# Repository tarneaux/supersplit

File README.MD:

# supersplit
You can read the article about this [here](https://tarneo.fr/posts/split_keyboard).

## What is this?
I tried to make a keyboard that is easy to use and compact. For this it has an (oversized) 9-key thumbfan and a (non-oversized) 4x6 matrix.

## Features
- 9-key thumbfan
- 4x6 matrix
- 2 trrs jacks on each side (four in total) for flexibility: on each side you can choose which one to use
- 2 elite-c controllers -> usb-c

## Downsides of this layout
As soon as I had soldered the keyboard, I noticed that the 4 outer thumb keys (On the right on the picture) were hard to reach and I am still not using them after a month of using this keyboard.
The 2 that are just next to the thumb home (the next 2 on the left of the previous) are easier to use but I prefer to use the 2 inner.
In short, that means I could have saved 6 keys on each side's thumfan.

## What I would do differently
I would let the matrix as is, remove the 4 outer thumfan keys and add a few degrees to the angle added to the next 2.

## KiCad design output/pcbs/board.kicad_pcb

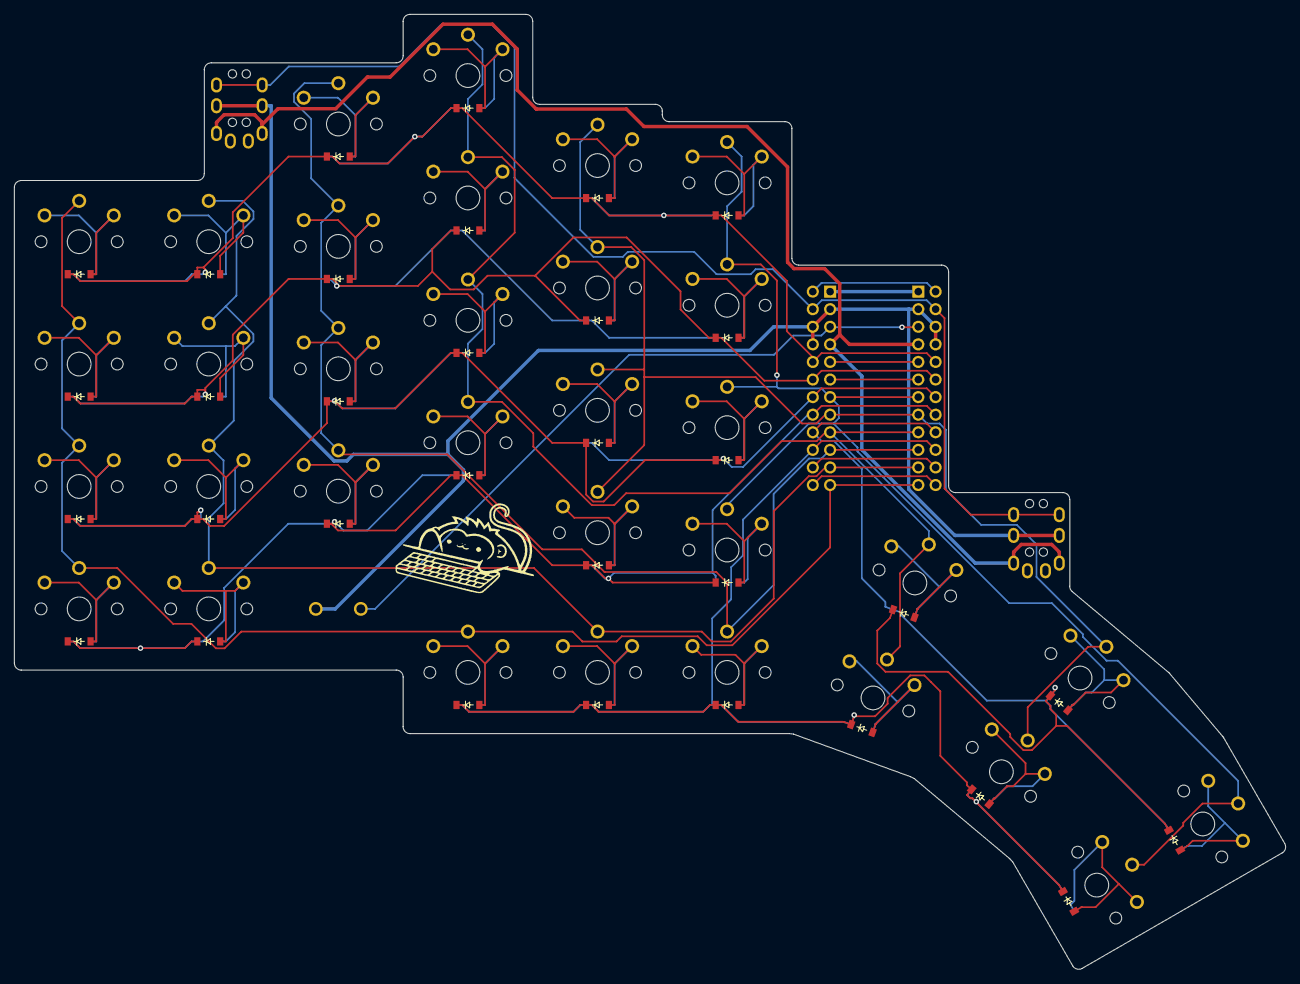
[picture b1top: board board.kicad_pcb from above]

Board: 2 copper layers, 183.6 x 137.9 mm, 73 parts (0 on the bottom side), 55 nets.

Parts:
B1: ResetSW
D1, D2, D3, D4, D5, D6, D7, D8, D9, D10, D11, D12, D13, D14, D15, D16, D17, D18, D19, D20, D21, D22, D23, D24, D25, D26, D27, D28, D29, D30, D31, D32, D33: ComboDiode
MCU1, MCU2: ProMicro
S1, S2, S3, S4, S5, S6, S7, S8, S9, S10, S11, S12, S13, S14, S15, S16, S17, S18, S19, S20, S21, S22, S23, S24, S25, S26, S27, S28, S29, S30, S31, S32, S33: PG1350
TRRS1, TRRS2, TRRS3, TRRS4: TRRS-PJ-320A-dual

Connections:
GND: B1.2, MCU1.2, MCU1.15, MCU1.16, MCU2.2, MCU2.15, MCU2.16, TRRS1.3, TRRS2.3, TRRS3.3, TRRS4.3
P0: MCU1.14, MCU2.14, TRRS1.4, TRRS2.4, TRRS3.4, TRRS4.4
P1: MCU1.13, MCU2.13
P2: D4.1, D8.1, D12.1, D16.1, D20.1, D24.1, MCU1.17, MCU2.17
P3: D3.1, D7.1, D11.1, D15.1, D19.1, D23.1, MCU1.18, MCU2.18
P4: D2.1, D6.1, D10.1, D14.1, D18.1, D22.1, MCU1.19, MCU2.19
P5: D1.1, D5.1, D9.1, D13.1, D17.1, D21.1, MCU1.20, MCU2.20
P6: D29.1, D31.1, D33.1, MCU1.21, MCU2.21
P7: D25.1, D26.1, D27.1, D28.1, D30.1, D32.1, MCU1.22, MCU2.22
P8: MCU1.23, MCU2.23
P9: MCU1.24, MCU2.24
P10: MCU1.12, MCU2.12, S1.2, S2.2, S3.2, S4.2, S25.2
P14: MCU1.10, MCU2.10, S9.2, S10.2, S11.2, S12.2, S27.2
P15: MCU1.9, MCU2.9, S13.2, S14.2, S15.2, S16.2, S28.2, S29.2
P16: MCU1.11, MCU2.11, S5.2, S6.2, S7.2, S8.2, S26.2
P18: MCU1.8, MCU2.8, S17.2, S18.2, S19.2, S20.2, S30.2, S31.2
P19: MCU1.7, MCU2.7, S21.2, S22.2, S23.2, S24.2, S32.2, S33.2
P20: MCU1.6, MCU2.6
P21: MCU1.5, MCU2.5
RAW: MCU1.1, MCU2.1
RST: B1.1, MCU1.3, MCU2.3
VCC: MCU1.4, MCU2.4, TRRS1.2, TRRS2.2, TRRS3.2, TRRS4.2
far_over: D29.2, S29.1
far_thumb: D28.2, S28.1
farther_over: D31.2, S31.1
farther_thumb: D30.2, S30.1
home_thumb: D27.2, S27.1
index_bottom: D17.2, S17.1
index_home: D18.2, S18.1
index_over: D20.2, S20.1
index_top: D19.2, S19.1
inner_bottom: D21.2, S21.1
inner_home: D22.2, S22.1
inner_over: D24.2, S24.1
inner_thumb: D25.2, S25.1
inner_top: D23.2, S23.1
middle_bottom: D13.2, S13.1
middle_home: D14.2, S14.1
middle_over: D16.2, S16.1
middle_top: D15.2, S15.1
near_thumb: D26.2, S26.1
outer_over: D33.2, S33.1
outer_thumb: D32.2, S32.1
pinky_bottom: D5.2, S5.1
pinky_home: D6.2, S6.1
pinky_off_bottom: D1.2, S1.1
pinky_off_home: D2.2, S2.1
pinky_off_over: D4.2, S4.1
pinky_off_top: D3.2, S3.1
pinky_over: D8.2, S8.1
pinky_top: D7.2, S7.1
ring_bottom: D9.2, S9.1
ring_home: D10.2, S10.1
ring_over: D12.2, S12.1
ring_top: D11.2, S11.1

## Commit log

2022-10-02 Create LICENSE
2022-10-05 Config as sent to PCB manufacturer
2022-10-07 As manufactured
2022-10-21 Add picture
2022-10-29 move image
2022-10-31 Add README.md
2022-10-31 correct mispushed readme
2022-10-31 complete readme
2023-04-15 Add article link to README
2023-07-02 Update post link and picture in README
2023-07-02 Make image in README display correctly
2024-03-15 Fix README file name
2024-03-15 Add disclaimer to README
